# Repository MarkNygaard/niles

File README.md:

# Niles

> Status: **pre-alpha** — under active development, not yet usable.

**Niles** (NYE-uls) — *Neural Intelligence, Lightweight Edge System* — is an open-source, AI-first home automation system designed to replace Home Assistant for users who want sub-second voice interactions, code/config over UI, and a voice assistant with real LLM intelligence as a first-class citizen.

It runs locally on small hardware (a Linux host or Kubernetes cluster), bridges Zigbee devices via Zigbee2MQTT, and exposes a voice interface through ESP32-S3 satellites (a reSpeaker XVF3800 with Niles's own firmware and an on-device "Niles" wake word) with a three-tier intent pipeline: regex → fast LLM → smart LLM.

It is set up from its own app. Settings keeps the base system — the broker your lights are reached through, and who hears and who thinks (ElevenLabs and Cerebras by default) — apart from the add-ons: optional extras such as Sonos, tado°, calendars and the Claude or ChatGPT assistants, and third-party add-ons installed from GitHub.

## Documentation

The docs are at [getniles.app/docs](https://getniles.app/docs), built from [site/](site/). Run it locally with `cd site; bun install; bun run dev` and browse at <http://localhost:4000>.

- **[ARCHITECTURE.md](ARCHITECTURE.md)** — the map and the rules: the crates, how a turn flows through them, the house rules and the big decisions. How to use Niles is in the docs site.
- **[AGENTS.md](AGENTS.md)** — how to work in this repo, for AI coding agents and the people who run them.
- **[CONTRIBUTING.md](CONTRIBUTING.md)** — dev setup and PR conventions.
- **[Naming your devices](https://getniles.app/docs/setting-up/naming)** — how to name things in Zigbee2MQTT so Niles finds them, and what to call them.
- **[Set up a satellite](firmware/xiao-wyoming/satellite-idf/README.md#set-up-a-satellite)** — flash a reSpeaker XVF3800 with the Niles firmware and add it to a room.
- **[MANIFEST.md](MANIFEST.md)** — what Niles can do, generated from `features.toml`.

## License

Dual-licensed under either of:

- Apache License, Version 2.0 ([LICENSE-APACHE](LICENSE-APACHE) or <http://www.apache.org/licenses/LICENSE-2.0>)
- MIT license ([LICENSE-MIT](LICENSE-MIT) or <https://opensource.org/licenses/MIT>)

at your option.

### Contribution

Unless you explicitly state otherwise, any contribution intentionally submitted for inclusion in this project by you, as defined in the Apache-2.0 license, shall be dual-licensed as above, without any additional terms or conditions.

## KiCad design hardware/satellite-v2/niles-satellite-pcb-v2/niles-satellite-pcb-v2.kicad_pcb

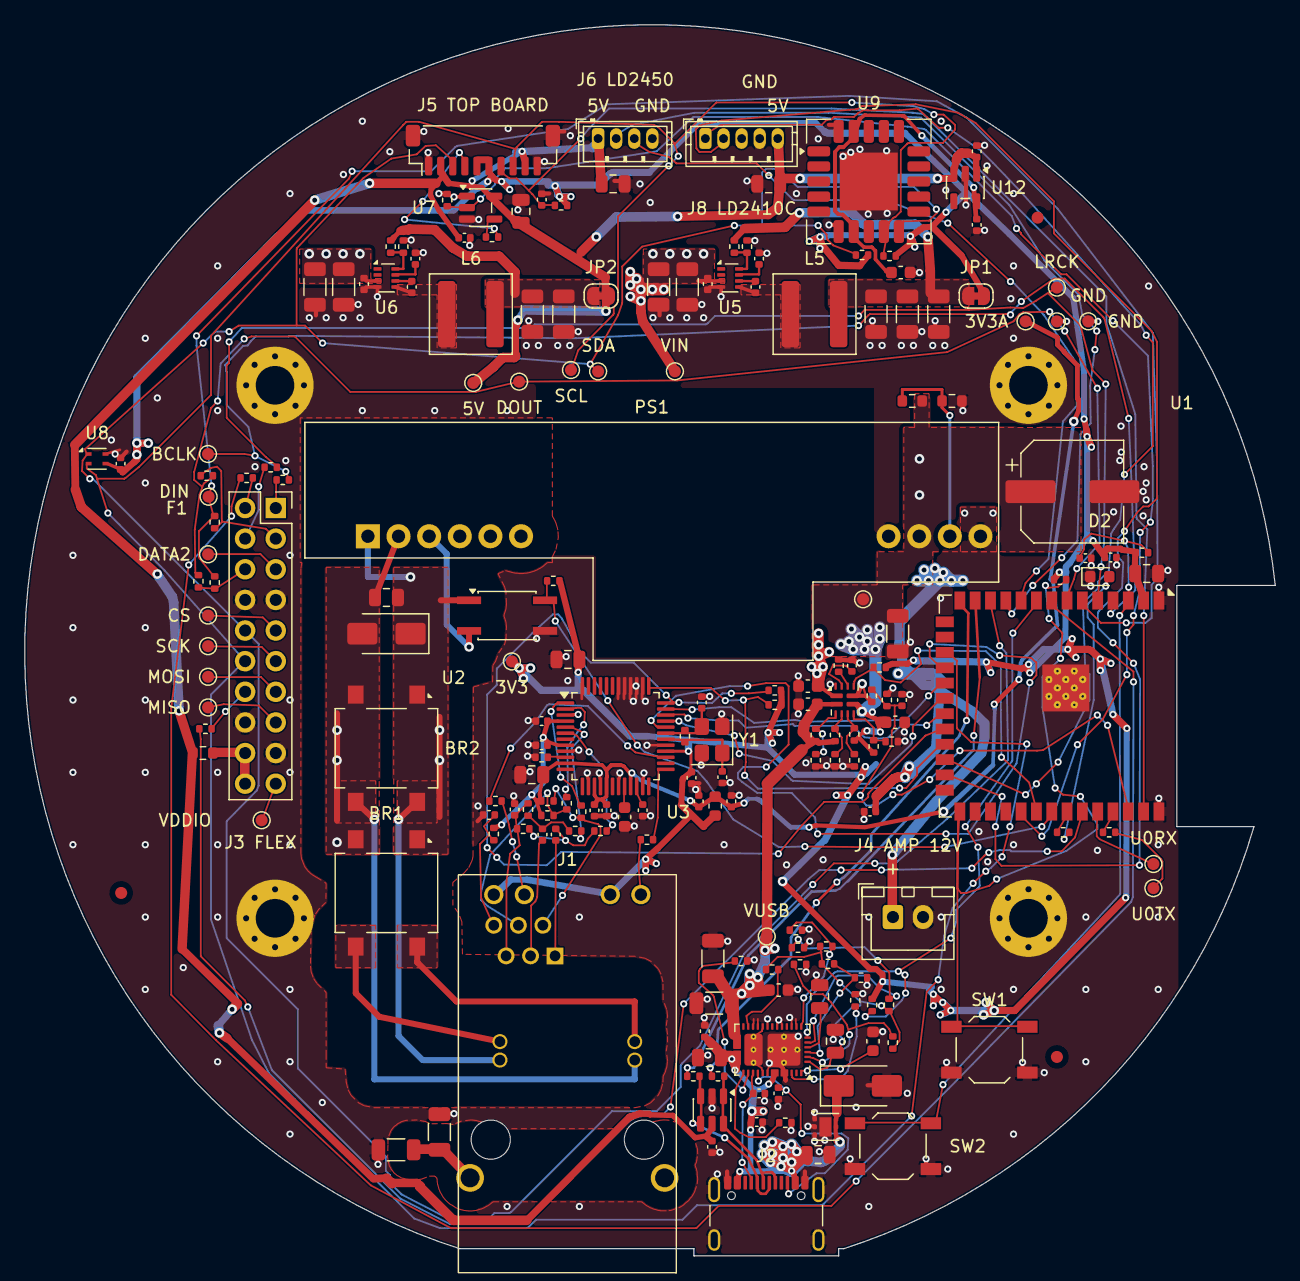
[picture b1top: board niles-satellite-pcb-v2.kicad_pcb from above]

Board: 4 copper layers, 103.7 x 102.1 mm, 198 parts (0 on the bottom side), 119 nets.

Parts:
BR1, BR2: DF01S; Diode_Bridge_OnSemi_SDIP-4L
C1: 10nF 100V; C_0805_2012Metric
C2: 560uF 16V polymer; CP_Elec_8x11.9
C3: 10uF 25V; C_1206_3216Metric
C4, C8, C41, C50, C51, C52, C53, C54, C55, C58, C80, C82, C83, C118: 100nF; C_0402_1005Metric
C5, C115, C116: 1uF 50V; C_0603_1608Metric
C20, C21, C30, C31, C98: 10uF 50V; C_1206_3216Metric
C22, C32, C110: 100nF 50V; C_0402_1005Metric
C23, C33: 100nF 16V; C_0402_1005Metric
C24, C34, C65: 22nF; C_0402_1005Metric
C25, C26, C27, C35, C36: 22uF 25V; C_1206_3216Metric
C40, C84: 22uF 25V; C_0805_2012Metric
C42, C114, C117: 1uF; C_0402_1005Metric
C56, C57: 10uF 25V; C_0805_2012Metric
C59: 4.7uF; C_0603_1608Metric
C60, C66: 10nF; C_0402_1005Metric
C61, C62: 27pF C0G; C_0402_1005Metric
C63, C64: 6.8nF; C_0402_1005Metric
C67: 1nF 2kV; C_1206_3216Metric
C81: 4.7uF 10V; C_0603_1608Metric
C85, C86: 10uF 10V; C_0805_2012Metric
C90, C91: 330pF C0G 50V; C_0402_1005Metric
C92, C93: 10uF 10V X7R; C_0805_2012Metric
C94: 10uF 6.3V; C_0603_1608Metric
C95: 4.7uF 50V; C_0805_2012Metric
C96, C97: 10nF 50V; C_0402_1005Metric
C99: DNP 10uF 50V; C_1206_3216Metric
C100: 100nF 50V; C_0603_1608Metric
C119: DNP 4.7uF 50V; C_0805_2012Metric
D1: SMAJ58A; D_SMA
D2: LED_green; LED_0603_1608Metric
D10: TVS2200DRVR; WSON-6-1EP_2x2mm_P0.65mm_EP1x1.6mm
D11: SS34; D_SMA
FB1: 120R@100MHz; L_0603_1608Metric
FID1, FID2, FID3: Fiducial; Fiducial_1mm_Mask2mm
H1, H2, H3, H4: Flex_standoff_M3; MountingHole_3.2mm_M3_Pad_Via
J1: 0826-1X1T-GJ-F; Bel_0826-1X1T-GJ-F
J2: USB_C_Receptacle; USB_C_Receptacle_GCT_USB4105-xx-A_16P_TopMnt_Horizontal
J3: Flex_2x10; PinSocket_2x10_P2.54mm_Vertical
J4: Conn_AMP_PWR; JST_XH_B2B-XH-A_1x02_P2.50mm_Vertical
J5: Conn_TopBoard; JST_SH_BM10B-SRSS-TB_1x10-1MP_P1.00mm_Vertical
J6: Conn_Radar; JST_ZH_B4B-ZR_1x04_P1.50mm_Vertical
J8: Conn_Radar2; JST_ZH_B5B-ZR_1x05_P1.50mm_Vertical
JP1, JP2: SolderJumper_bridged; SolderJumper-2_P1.3mm_Bridged_RoundedPad1.0x1.5mm
L5: 4.7uH; L_Wuerth_XHMI-6060
L6: 6.8uH; L_Wuerth_XHMI-6060
PS1: Ag5412; Converter_DCDC_Silvertel_Ag54xx
R1: DNP >=68k trim; R_0603_1608Metric
R2: DNP trim; R_0603_1608Metric
R3: 47k; R_0402_1005Metric
R4, R6: 120k 0.1%; R_0402_1005Metric
R5, R7: 10k 0.1%; R_0402_1005Metric
R8: 24.3k 1%; R_0402_1005Metric
R9, R15: 10k 1%; R_0402_1005Metric
R10: 22.1k 1%; R_0402_1005Metric
R11, R40, R41, R53, R54, R98, R99, R100, R101, R102: 10k; R_0402_1005Metric
R12, R90, R92, R94, R96: 100k 1%; R_0402_1005Metric
R13: 22k 1%; R_0402_1005Metric
R14: 30.1k 1%; R_0402_1005Metric
R16, R52: 1M; R_0402_1005Metric
R17: 0R; R_0603_1608Metric
R20: 75.0k 1%; R_0402_1005Metric
R21: 24.0k 1%; R_0402_1005Metric
R30: 53.6k 1%; R_0402_1005Metric
R31: 10.2k 1%; R_0402_1005Metric
R42: 499R; R_0402_1005Metric
R43, R44, R55, R56, R57, R58, R74, R75: 0R; R_0402_1005Metric
R45: 1k; R_0402_1005Metric
R50: 12.4k 1%; R_0402_1005Metric
R59, R60, R61, R62: 49.9R 1%; R_0402_1005Metric
R63: 10R 1%; R_0402_1005Metric
R64, R65: 330R; R_0402_1005Metric
R66: 1M; R_1206_3216Metric
R70, R71, R72, R73: DNP 0R; R_0402_1005Metric
R76, R77: 22R; R_0402_1005Metric
R80, R81: 4.7k; R_0402_1005Metric
R82: 220R; R_0402_1005Metric
R83: 100k; R_0402_1005Metric
R91, R97: 5.10k 1%; R_0402_1005Metric
R93: 23.2k 1%; R_0402_1005Metric
R95: 12.1k 1%; R_0402_1005Metric
SW1: BOOT; SW_SPST_TL3342
SW2: RESET; SW_SPST_TL3342
TP1, TP2, TP3, TP4, TP5, TP6, TP7, TP8, TP9, TP10, TP11, TP12, TP13, TP14, TP20, TP21, TP22, TP23, TP24, TP25, TP26, TP27: TestPoint; TestPoint_Pad_D1.0mm
U1: ESP32-S3-WROOM-1-N16R8; ESP32-S3-WROOM-1
U2: KPC357NT; SO-4_4.4x3.6mm_P2.54mm
U3: W5500; LQFP-48_7x7mm_P0.5mm
U4: TPS2121RUXR; Texas_VQFN-HR-12_2x2.5mm_P0.5mm
U5, U6: TPS62933FDRLR; SOT-583-8
U7: SN74AHCT1G125DBVR; SOT-23-5
U8: SHT40-AD1B; Sensirion_DFN-4_1.5x1.5mm_P0.8mm_SHT4x_NoCentralPad
U9: SCD41; Sensirion_SCD4x-1EP_10.1x10.1mm_P1.25mm_EP4.8x4.8mm
U10: USBLC6-2SC6; SOT-23-6
U11: TPS25730DREFR; Texas_REF0038A_WQFN-38-2EP_6x4mm_P0.4
U12: TLV75533PDBVR; SOT-23-5
Y1: 25MHz CL18pF; Crystal_SMD_3225-4Pin_3.2x2.5mm

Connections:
+3V3: C40.1, C41.1, C57.1, C58.1, C80.1, FB1.1, J1.18, J1.20, J5.5, J5.6, JP1.2, R3.2, R11.2, R16.2, R40.1, R41.1, R53.2, R54.2, R80.2, R81.2, R102.2, TP5.1, U1.2, U3.28, U8.3
+3V3A: C50.1, C51.1, C52.1, C53.1, C54.1, C55.1, C56.1, FB1.2, R59.2, R60.2, R63.2, TP6.1, U3.4, U3.8, U3.11, U3.15, U3.17, U3.21
+3V3_BUCK: C25.1, C26.1, C27.1, JP1.1, L5.2, R20.1
+3V3_CO2: C81.1, C117.1, U9.7, U9.19, U12.5
+5V: C82.1, C84.1, C85.1, C86.1, C114.1, C118.1, J5.2, J5.9, J6.1, J8.5, JP2.2, R17.1, TP4.1, U7.5, U10.5, U12.1, U12.3
+5V_BUCK: C35.1, C36.1, JP2.1, L6.2, R30.1
BOOT: R41.2, SW1.1, U1.27
BTN_ADC: C83.1, J5.7, R16.1, U1.39
CHASSIS: C67.1, J1.SH, R66.1
EN: C42.1, R40.2, SW2.1, U1.3
ESP_MCLK: R70.1, U1.8
ESP_TXD0: R42.1, U1.37
ESP_X1D13: R71.1, U1.35
ETH_1V2O: C60.1, U3.22
ETH_ACTLED: R65.2, U3.27
ETH_ACT_K: J1.19, R65.1
ETH_CS: U1.18, U3.32
ETH_C_RXN: C64.1, R58.2, R62.1
ETH_C_RXP: C63.1, R57.2, R61.1
ETH_EXRES1: R50.1, U3.10
ETH_INT: R53.1, U1.22, U3.36
ETH_J_RXN: C64.2, J1.5
ETH_J_RXP: C63.2, J1.4
ETH_J_TXN: J1.10, R56.2, R60.1
ETH_J_TXP: J1.11, R55.2, R59.1
ETH_LINKLED: R64.2, U3.25
ETH_LINK_K: J1.17, R64.1
ETH_MISO: U1.21, U3.34
ETH_MOSI: U1.19, U3.35
ETH_RST: R54.1, U1.23, U3.37
ETH_RXCT: C66.1, J1.6, R61.2, R62.2
ETH_RXN: R58.1, U3.5
ETH_RXP: R57.1, U3.6
ETH_SCLK: U1.20, U3.33
ETH_TOCAP: C59.1, U3.20
ETH_TXCT: C65.1, J1.12, R63.1
ETH_TXN: R56.1, U3.1
ETH_TXP: R55.1, U3.2
ETH_XI: C61.1, R52.1, U3.30, Y1.1
ETH_XO: C62.1, R52.2, U3.31, Y1.3
FLEX_5V: J3.18, J3.20, R17.2
FLEX_BCLK: J3.1, R76.1
FLEX_DATA0: J3.6, R72.1, R74.1
FLEX_DATA1: J3.3, R73.1, R75.1
FLEX_DATA2: J3.5, TP24.1
FLEX_LRCK: J3.4, R77.1
FLEX_MCLK: J3.2, R70.2
FLEX_SPI_CLK: J3.11, TP22.1
FLEX_SPI_CS_N: J3.9, TP23.1
FLEX_SPI_MISO: J3.15, TP20.1
FLEX_SPI_MOSI: J3.13, TP21.1
FLEX_VDDIO: J3.19, TP25.1
FLEX_X1D13: J3.14, R71.2
GND: C2.2, C3.2, C4.2, C5.2, C8.2, C20.2, C21.2, C22.2, C24.2, C25.2, C26.2, C27.2, C30.2, C31.2, C32.2, C34.2, C35.2, C36.2, C40.2, C41.2, C42.2, C50.2, C51.2, C52.2, C53.2, C54.2, C55.2, C56.2, C57.2, C58.2, C59.2, C60.2, C61.2, C62.2, C65.2, C66.2, C67.2, C80.2, C81.2, C82.2, C83.2, C84.2, C85.2, C86.2, C90.2, C91.2, C92.2, C93.2, C94.2, C95.2, C96.2, C97.2, C98.2, C99.2, C100.2, C110.2, C114.2, C115.2, C116.2, C117.2, C118.2, C119.2, D2.1, D10.1, D10.2, D10.3, D10.7, D11.2, H1.1, H2.1, H3.1, H4.1, J2.A1, J2.A12, J2.B1, J2.B12, J2.SH, J3.7, J3.8, J3.16, J3.17, J4.2, J5.1, J5.10, J5.MP, J6.4, J8.4, PS1.7, PS1.10, R2.2, R5.2, R7.2, R9.2, R10.2, R13.2, R15.2, R21.2, R31.2, R50.2, R66.2, R83.2, R91.2, R93.2, R95.2, R97.2, R99.2, R100.2, R101.2, SW1.2, SW2.2, TP7.1, TP8.1, U1.1, U1.40, U1.41, U2.3, U3.3, U3.9, U3.14, U3.16, U3.19, U3.23, U3.29, U3.38, U3.39, U3.40, U3.41, U3.42, U3.48, U4.12, U5.4, U6.4, U7.1, U7.3, U8.4, U9.6, U9.20, U9.21, U10.2, U11.8, U11.9, U11.11, U11.12, U11.14, U11.16, U11.17, U11.31, U11.34, U11.39, U12.2, Y1.2, Y1.4
I2C_SCL: J3.12, J5.8, R81.1, TP14.1, U1.17, U8.2, U9.9
I2C_SDA: J3.10, J5.3, R80.1, TP13.1, U1.12, U8.1, U9.10
I2S_BCLK: R76.2, TP9.1, U1.4
I2S_DIN: R72.2, R75.2, TP11.1, U1.6
I2S_DOUT: R73.2, R74.2, TP12.1, U1.7
I2S_LRCK: R77.2, TP10.1, U1.5
LED_DATA: R83.1, U1.31, U7.2
LED_DATA_5V: J5.4, R82.2
LED_DATA_Y: R82.1, U7.4
MUX_CP2: R14.2, R15.1, U4.3
MUX_ILM: R10.1, U4.10
MUX_OV1: R4.2, R5.1, U4.5
MUX_OV2: R6.2, R7.1, U4.4
MUX_PR1: R8.2, R9.1, U4.6
MUX_SS: C4.1, U4.11
PD_ADCIN1: R90.2, R91.1, U11.2
PD_ADCIN2: R92.2, R93.1, U11.3
PD_ADCIN3: R94.2, R95.1, U11.5
PD_ADCIN4: R96.2, R97.1, U11.7
PD_DRAIN: U11.15, U11.30, U11.40
PD_FAULT_IN: R98.2, U11.18
PD_LDO_1V5: C93.1, U11.4
PD_LDO_3V3: C92.1, R90.1, R92.1, R94.1, R96.1, R98.1, U11.1
PD_RSVD1: R99.1, U11.26
PD_RSVD2: R100.1, U11.27
PD_RSVD3: R101.1, U11.36
PD_VIN_3V3: C94.1, U11.38
POE_ADJ: PS1.9, R1.1, R2.1
POE_AT: R3.1, U1.33, U2.4
POE_ATDET: PS1.3, U2.2
POE_VC12: BR1.4, J1.13
POE_VC36: BR1.3, J1.14
POE_VC45: BR2.3, J1.15
POE_VC78: BR2.4, J1.16
POE_VIN+: BR1.1, BR2.1, C1.1, D1.1, PS1.1, U2.1
POE_VIN-: BR1.2, BR2.2, C1.2, D1.2, PS1.2
PWR_SRC: R11.1, U1.32, U4.9
RADAR2_RX: J8.1, U1.24
RADAR2_TX: J8.2, U1.25
RADAR_RX: J6.3, U1.10
RADAR_TX: J6.2, U1.11
STATUS_LED: R45.1, U1.34
STATUS_LED_A: D2.2, R45.2
U5_BST: C23.1, U5.6
U5_FB: R20.2, R21.1, U5.8
U5_SS: C24.1, U5.7
U5_SW: C23.2, L5.1, U5.5
U6_BST: C33.1, U6.6
U6_FB: R30.2, R31.1, U6.8
U6_SS: C34.1, U6.7
U6_SW: C33.2, L6.1, U6.5
UART0_RX: TP27.1, U1.36
UART0_TX: R42.2, TP26.1
USB_CAP_MIS: R102.1, U1.9, U11.6
USB_CC1: C90.1, J2.A5, U11.28
USB_CC2: C91.1, J2.B5, U11.29
USB_D+: J2.A6, J2.B6, R44.2, U10.1, U10.6
USB_D-: J2.A7, J2.B7, R43.2, U10.3, U10.4
USB_ESP_D+: R44.1, U1.14
USB_ESP_D-: R43.1, U1.13
VBUS_RAW: C95.1, C96.1, C97.1, C119.1, D10.4, D10.5, D10.6, D11.1, J2.A4, J2.A9, J2.B4, J2.B9, U11.23, U11.32
VIN: C20.1, C21.1, C22.1, C30.1, C31.1, C32.1, C110.1, C116.1, J4.1, R12.1, TP1.1, U4.1, U4.8, U5.3, U6.3
VIN_SENSE: C8.1, R12.2, R13.1, U1.38
VPOE_12V: C2.1, C3.1, C5.1, PS1.8, R1.2, R4.1, R8.1, TP2.1, U4.7
VUSB: C98.1, C99.1, C100.1, C115.1, R6.1, R14.1, TP3.1, U4.2, U11.20

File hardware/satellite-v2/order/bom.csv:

Comment,Designator,Footprint,LCSC Part #
DF01S,"BR1,BR2",Diode_Bridge_OnSemi_SDIP-4L,C124477
10nF 100V,C1,C_0805_2012Metric,C18741
560uF 16V polymer,C2,CP_Elec_8x11.9,C178349
10uF 25V,C3,C_1206_3216Metric,C77093
100nF 16V,"C4,C8,C23,C33,C41,C50,C51,C52,C53,C54,C55,C58,C80,C82,C83,C118",C_0402_1005Metric,C1525
1uF 50V,"C5,C115,C116",C_0603_1608Metric,C105174
10uF 50V,"C20,C21,C30,C31,C98",C_1206_3216Metric,C89632
100nF 50V,"C22,C32,C110",C_0402_1005Metric,C307331
22nF,"C24,C34,C65",C_0402_1005Metric,C1532
22uF 25V,"C25,C26,C27,C35,C36",C_1206_3216Metric,C12891
22uF 25V,"C40,C84",C_0805_2012Metric,C45783
1uF,"C42,C114,C117",C_0402_1005Metric,C52923
10uF 25V,"C56,C57",C_0805_2012Metric,C15850
4.7uF 10V,"C59,C81",C_0603_1608Metric,C19666
10nF 50V,"C60,C66,C96,C97",C_0402_1005Metric,C15195
27pF C0G,"C61,C62",C_0402_1005Metric,C86287
6.8nF,"C63,C64",C_0402_1005Metric,C318580
1nF 2kV,C67,C_1206_3216Metric,C23631
10uF 10V X7R,"C85,C86,C92,C93",C_0805_2012Metric,C32635
330pF C0G 50V,"C90,C91",C_0402_1005Metric,C76965
10uF 6.3V,C94,C_0603_1608Metric,C77041
4.7uF 50V,C95,C_0805_2012Metric,C162320
100nF 50V,C100,C_0603_1608Metric,C14663
SMAJ58A,D1,D_SMA,C10762
LED_green,D2,LED_0603_1608Metric,C125098
TVS2200DRVR,D10,WSON-6-1EP_2x2mm_P0.65mm_EP1x1.6mm,C523793
SS34,D11,D_SMA,C8678
120R@100MHz,FB1,L_0603_1608Metric,C14709
0826-1X1T-GJ-F,J1,Bel_0826-1X1T-GJ-F,C6377355
USB_C_Receptacle,J2,USB_C_Receptacle_GCT_USB4105-xx-A_16P_TopMnt_Horizontal,C3020560
Flex_2x10,J3,PinSocket_2x10_P2.54mm_Vertical,C3322059
Conn_AMP_PWR,J4,JST_XH_B2B-XH-A_1x02_P2.50mm_Vertical,C158012
Conn_TopBoard,J5,JST_SH_BM10B-SRSS-TB_1x10-1MP_P1.00mm_Vertical,C160396
Conn_Radar,J6,JST_ZH_B4B-ZR_1x04_P1.50mm_Vertical,C157997
Conn_Radar2,J8,JST_ZH_B5B-ZR_1x05_P1.50mm_Vertical,C157990
4.7uH,L5,L_Wuerth_XHMI-6060,C6827938
6.8uH,L6,L_Wuerth_XHMI-6060,C2041388
Ag5412,PS1,Converter_DCDC_Silvertel_Ag54xx,C40163463
47k,R3,R_0402_1005Metric,C25792
120k 0.1%,"R4,R6",R_0402_1005Metric,C852501
10k 0.1%,"R5,R7",R_0402_1005Metric,C190095
24.3k 1%,R8,R_0402_1005Metric,C276264
10k 1%,"R9,R11,R15,R40,R41,R53,R54,R98,R99,R100,R101,R102",R_0402_1005Metric,C25744
22.1k 1%,R10,R_0402_1005Metric,C163478
100k 1%,"R12,R83,R90,R92,R94,R96",R_0402_1005Metric,C25741
22k 1%,R13,R_0402_1005Metric,C25768
30.1k 1%,R14,R_0402_1005Metric,C138009
1M,"R16,R52",R_0402_1005Metric,C26083
0R,R17,R_0603_1608Metric,C21189
75.0k 1%,R20,R_0402_1005Metric,C137935
24.0k 1%,R21,R_0402_1005Metric,C138026
53.6k 1%,R30,R_0402_1005Metric,C273330
10.2k 1%,R31,R_0402_1005Metric,C138069
499R,R42,R_0402_1005Metric,C137970
0R,"R43,R44,R55,R56,R57,R58,R74,R75",R_0402_1005Metric,C17168
1k,R45,R_0402_1005Metric,C11702
12.4k 1%,R50,R_0402_1005Metric,C138060
49.9R 1%,"R59,R60,R61,R62",R_0402_1005Metric,C25120
10R 1%,R63,R_0402_1005Metric,C25077
330R,"R64,R65",R_0402_1005Metric,C25104
1M,R66,R_1206_3216Metric,C17927
22R,"R76,R77",R_0402_1005Metric,C25092
4.7k,"R80,R81",R_0402_1005Metric,C25900
220R,R82,R_0402_1005Metric,C25091
5.10k 1%,"R91,R97",R_0402_1005Metric,C25905
23.2k 1%,R93,R_0402_1005Metric,C25873
12.1k 1%,R95,R_0402_1005Metric,C132157
RESET,"SW1,SW2",SW_SPST_TL3342,C2886898
ESP32-S3-WROOM-1-N16R8,U1,ESP32-S3-WROOM-1,C2913202
KPC357NT,U2,SO-4_4.4x3.6mm_P2.54mm,C136411
W5500,U3,LQFP-48_7x7mm_P0.5mm,C32843
TPS2121RUXR,U4,Texas_VQFN-HR-12_2x2.5mm_P0.5mm,C485916
TPS62933FDRLR,"U5,U6",SOT-583-8,C5219272
SN74AHCT1G125DBVR,U7,SOT-23-5,C7484
SHT40-AD1B,U8,Sensirion_DFN-4_1.5x1.5mm_P0.8mm_SHT4x_NoCentralPad,C2909890
SCD41,U9,Sensirion_SCD4x-1EP_10.1x10.1mm_P1.25mm_EP4.8x4.8mm,C3659294
USBLC6-2SC6,U10,SOT-23-6,C7519
TPS25730DREFR,U11,Texas_REF0038A_WQFN-38-2EP_6x4mm_P0.4,C22438973
TLV75533PDBVR,U12,SOT-23-5,C404027
25MHz CL18pF,Y1,Crystal_SMD_3225-4Pin_3.2x2.5mm,C70593

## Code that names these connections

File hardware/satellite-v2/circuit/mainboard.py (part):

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ESP_MCLK, ESP_X1D13 = Net("ESP_MCLK"), Net("ESP_X1D13")
UART_TX, UART_RX = Net("UART0_TX"), Net("UART0_RX")
EXP16 = USB_CAP_MIS   # IO16 reads the PD mismatch flag
for pin, net in (("IO4", I2S_BCLK), ("IO5", I2S_LRCK), ("IO6", I2S_DIN), ("IO7", I2S_DOUT),
                 ("IO15", ESP_MCLK), ("IO16", EXP16), ("IO17", RADAR_RX), ("IO18", RADAR_TX),
                 ("IO8", SDA), ("IO9", SCL),
                 ("IO10", ETH_CS), ("IO11", ETH_MOSI), ("IO12", ETH_SCLK), ("IO13", ETH_MISO),
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C("C61", "27pF C0G", xi, GND)
C("C62", "27pF C0G", xo, GND)
# SPI and control.
for pin, net in (("SCSn", ETH_CS), ("SCLK", ETH_SCLK), ("MISO", ETH_MISO), ("MOSI", ETH_MOSI),
                 ("INTn", ETH_INT), ("RSTn", ETH_RST)):
    net += U3[pin]
R("R53", "10k", ETH_INT, V3)
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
